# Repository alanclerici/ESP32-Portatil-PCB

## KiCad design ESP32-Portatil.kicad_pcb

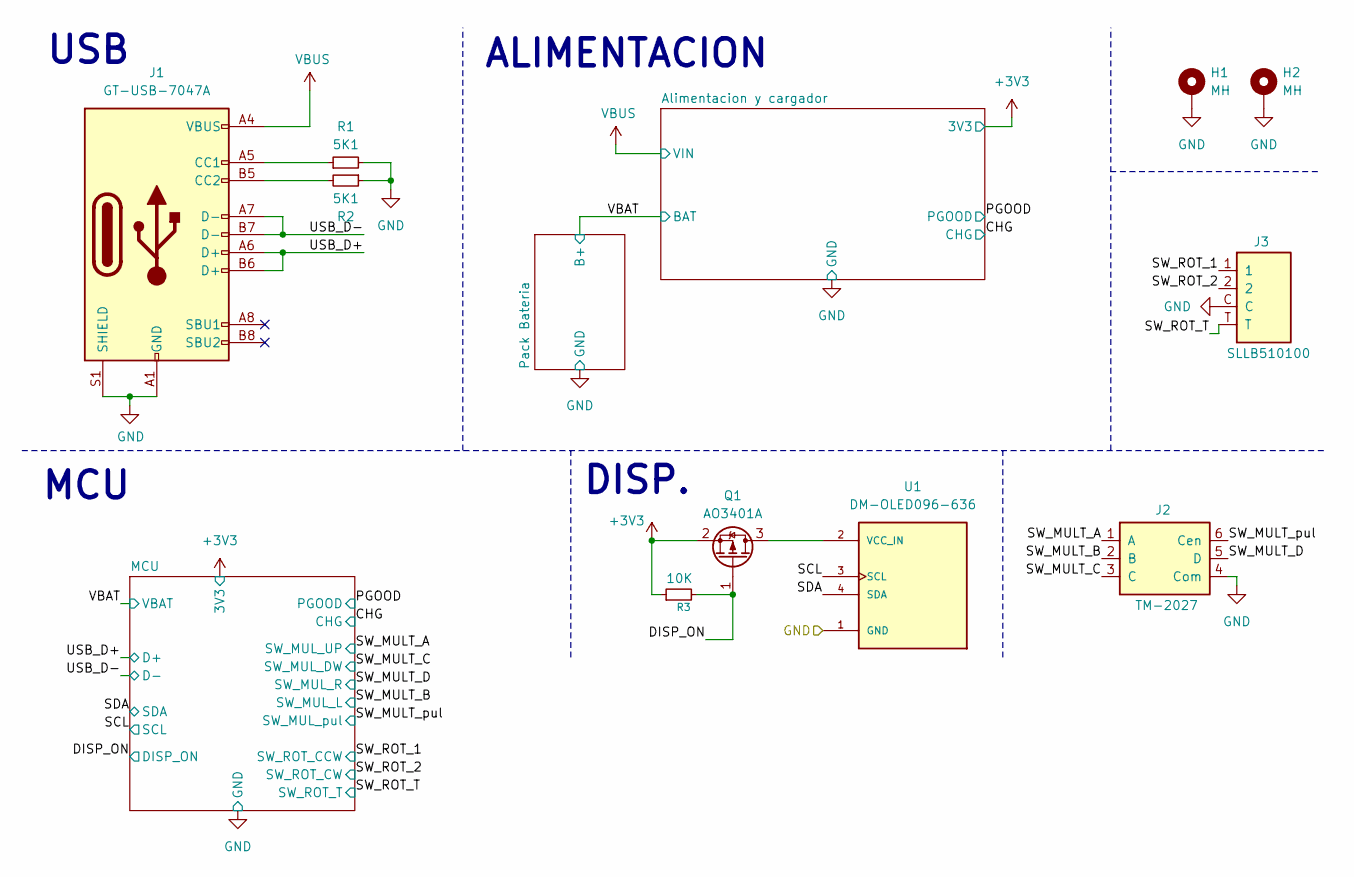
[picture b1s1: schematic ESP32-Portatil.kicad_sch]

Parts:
H1, H2: MH; MountingHole_3.2mm_M3_Pad_Via
J1: GT-USB-7047A; USB_C_Receptacle_GCT_USB4110; LCSC GT-USB-7047A
J2: TM-2027; JLCPCB Part # C318948
J3: SLLB510100; JLCPCB Part # C125039
Q1: AO3401A; SOT-23; JLCPCB Part # C15127
R1, R2: 5K1; R_0402_1005Metric; LCSC 0603WAF5101T5E
R3: 10K; R_0402_1005Metric; JLCPCB Part # C25744
U1: DM-OLED096-636; MODULE_DM-OLED096-636; PARTREV 2018-09-10

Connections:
+3V3: Q1.2 (S), R3.1; also elsewhere on the board
/DISP_ON: Q1.1 (G), R3.2; also elsewhere on the board
/SCL: U1.3 (SCL); also elsewhere on the board
/SDA: U1.4 (SDA); also elsewhere on the board
/SW_MULT_A: J2.1 (A); also elsewhere on the board
/SW_MULT_B: J2.2 (B); also elsewhere on the board
/SW_MULT_C: J2.3 (C); also elsewhere on the board
/SW_MULT_D: J2.5 (D); also elsewhere on the board
/SW_MULT_pul: J2.6 (Cen); also elsewhere on the board
/SW_ROT_1: J3.1; also elsewhere on the board
/SW_ROT_2: J3.2; also elsewhere on the board
/SW_ROT_T: J3.T; also elsewhere on the board
/USB_D+: J1.A6 (D+), J1.B6 (D+); also elsewhere on the board
/USB_D-: J1.A7 (D-), J1.B7 (D-); also elsewhere on the board
GND: H1.1, H2.1, J1.A1 (GND), J1.A12 (GND), J1.B1 (GND), J1.B12 (GND), J1.S1 (SHIELD), J2.4 (Com), J3.C, R1.2, R2.1, U1.1 (GND); also elsewhere on the board
unnamed: J1.A5 (CC1), R1.1
unnamed: J1.B5 (CC2), R2.2
unnamed: Q1.3 (D), U1.2 (VCC_IN)
VBUS: J1.A4 (VBUS), J1.A9 (VBUS), J1.B4 (VBUS), J1.B9 (VBUS); also elsewhere on the board

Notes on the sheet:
DISP.
MCU
USB
ALIMENTACION

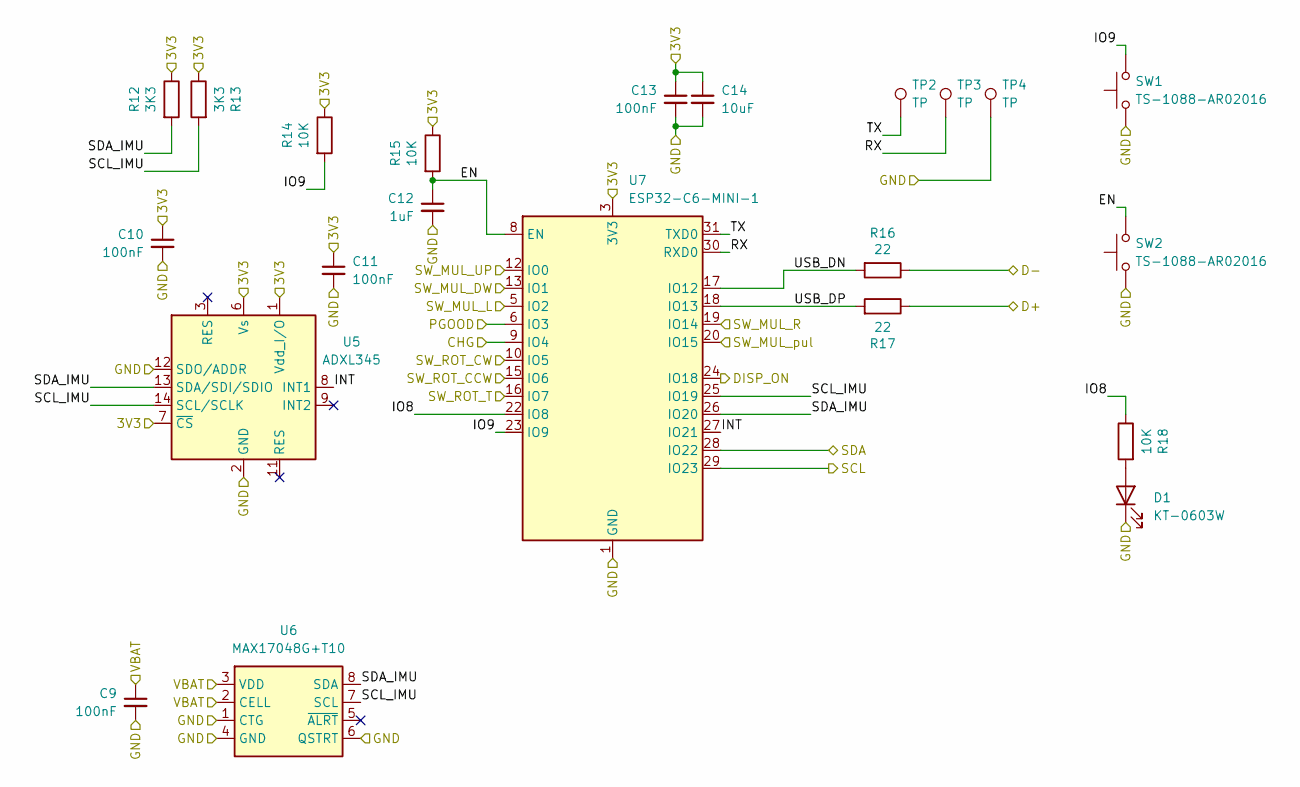
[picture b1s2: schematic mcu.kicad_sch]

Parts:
C9, C10, C11, C13: 100nF; C_0402_1005Metric; JLCPCB Part # C1525
C12: 1uF; C_0402_1005Metric; JLCPCB Part # C52923
C14: 10uF; C_0603; JLCPCB Part # C19702
D1: KT-0603W; LED_0603_1608Metric; LCSC SZYY0603G1
R12, R13: 3K3; R_0402_1005Metric; JLCPCB Part # C25890
R14, R15, R18: 10K; R_0402_1005Metric; LCSC 0603WAF4700T5E
R16, R17: 22; R_0402_1005Metric; LCSC 0402WGF270JTCE
SW1, SW2: TS-1088-AR02016; JLCPCB Part # C720477
TP2, TP3, TP4: TP; TestPoint_Pad_D1.5mm
U5: ADXL345; LGA-14_3x5mm_P0.8mm_LayoutBorder1x6y; JLCPCB Part # C9667
U6: MAX17048G+T10; TDFN-8-1EP_2x2mm_P0.5mm_EP0.8x1.2mm; JLCPCB Part # C2682616
U7: ESP32-C6-MINI-1; JLCPCB Part # C5736265

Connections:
+3V3: C10.1, C11.1, C13.1, C14.1, R12.1, R13.1, R14.1, R15.1, U5.1 (Vdd_I/O), U5.6 (Vs), U5.7 (~CS), U7.3 (3V3); also elsewhere on the board
/CHG: U7.9 (IO4); also elsewhere on the board
/DISP_ON: U7.24 (IO18); also elsewhere on the board
/MCU/EN: C12.1, R15.2, SW2.2, U7.8 (EN)
/MCU/INT: U5.8 (INT1), U7.27 (IO21)
/MCU/IO8: R18.1, U7.22 (IO8)
/MCU/IO9: R14.2, SW1.2, U7.23 (IO9)
/MCU/RX: TP3.1, U7.30 (RXD0)
/MCU/SCL_IMU: R13.2, U5.14 (SCL/SCLK), U6.7 (SCL), U7.25 (IO19)
/MCU/SDA_IMU: R12.2, U5.13 (SDA/SDI/SDIO), U6.8 (SDA), U7.26 (IO20)
/MCU/TX: TP2.1, U7.31 (TXD0)
/MCU/USB_DN: R16.2, U7.17 (IO12)
/MCU/USB_DP: R17.2, U7.18 (IO13)
/PGOOD: U7.6 (IO3); also elsewhere on the board
/SCL: U7.29 (IO23); also elsewhere on the board
/SDA: U7.28 (IO22); also elsewhere on the board
/SW_MULT_A: U7.12 (IO0); also elsewhere on the board
/SW_MULT_B: U7.5 (IO2); also elsewhere on the board
/SW_MULT_C: U7.13 (IO1); also elsewhere on the board
/SW_MULT_D: U7.19 (IO14); also elsewhere on the board
/SW_MULT_pul: U7.20 (IO15); also elsewhere on the board
/SW_ROT_1: U7.15 (IO6); also elsewhere on the board
/SW_ROT_2: U7.10 (IO5); also elsewhere on the board
/SW_ROT_T: U7.16 (IO7); also elsewhere on the board
/USB_D+: R17.1; also elsewhere on the board
/USB_D-: R16.1; also elsewhere on the board
/VBAT: C9.1, U6.2 (CELL), U6.3 (VDD); also elsewhere on the board
GND: C9.2, C10.2, C11.2, C12.2, C13.2, C14.2, D1.1 (K), SW1.1, SW2.1, TP4.1, U5.2 (GND), U5.4 (GND), U5.5 (GND), U5.12 (SDO/ADDR), U6.1 (CTG), U6.4 (GND), U6.6 (QSTRT), U6.9 (EP), U7.1 (GND), U7.2 (GND), U7.11 (GND), U7.14 (GND), U7.36 (GND), U7.37 (GND), U7.38 (GND), U7.39 (GND), U7.40 (GND), U7.41 (GND), U7.42 (GND), U7.43 (GND), U7.44 (GND), U7.45 (GND), U7.46 (GND), U7.47 (GND), U7.48 (GND), U7.49 (GND), U7.50 (GND), U7.51 (GND), U7.52 (GND), U7.53 (GND); also elsewhere on the board
unnamed: D1.2 (A), R18.2

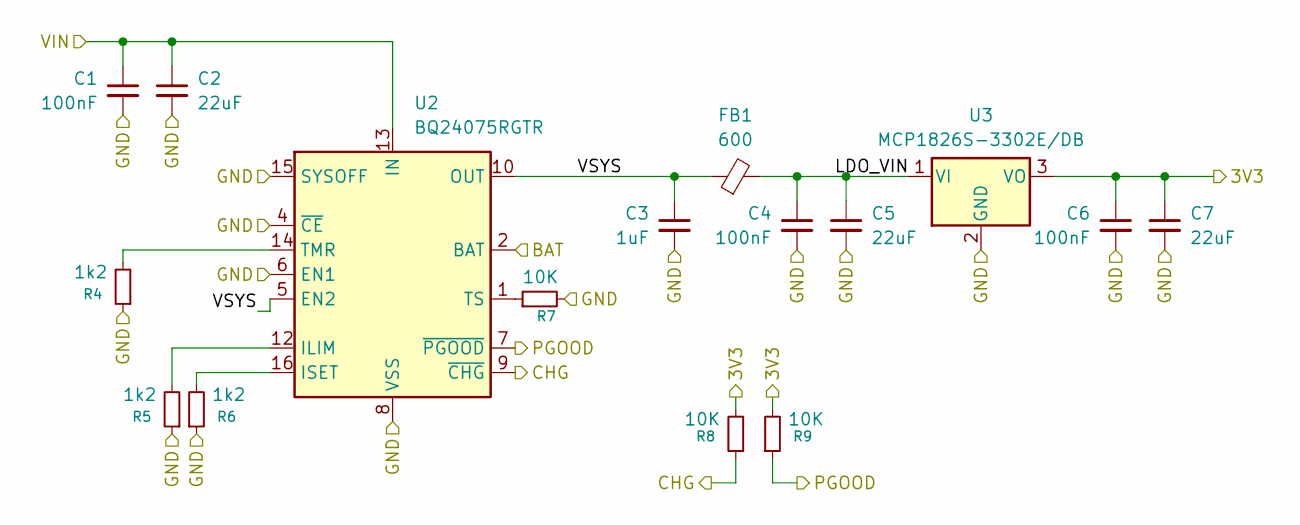
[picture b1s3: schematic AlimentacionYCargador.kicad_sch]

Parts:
C1, C4, C6: 100nF; C_0402_1005Metric; JLCPCB Part # C1525
C2, C5, C7: 22uF; C_0805_2012Metric; JLCPCB Part # C45783
C3: 1uF; C_0402_1005Metric; JLCPCB Part # C52923
FB1: 600; L_0805_2012Metric; JLCPCB Part # C1017
R4, R5, R6: 1k2; R_0402_1005Metric; JLCPCB Part # C25862
R7, R8, R9: 10K; R_0402_1005Metric; JLCPCB Part # C25744
U2: BQ24075RGTR; VQFN-16-1EP_3x3mm_P0.5mm_EP1.6x1.6mm; JLCPCB Part # C15464
U3: MCP1826S-3302E/DB; SOT-223-3_TabPin2; JLCPCB Part # C638624

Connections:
+3V3: C6.1, C7.1, R8.2, R9.2, U3.3 (VO); also elsewhere on the board
/Alimentacion y cargador/LDO_VIN: C4.1, C5.1, FB1.2, U3.1 (VI)
/Alimentacion y cargador/VSYS: C3.1, FB1.1, U2.5 (EN2), U2.10 (OUT), U2.11 (OUT)
/CHG: R8.1, U2.9 (~CHG); also elsewhere on the board
/PGOOD: R9.1, U2.7 (~PGOOD); also elsewhere on the board
/VBAT: U2.2 (BAT), U2.3 (BAT); also elsewhere on the board
GND: C1.2, C2.2, C3.2, C4.2, C5.2, C6.2, C7.2, R4.1, R5.1, R6.1, R7.2, U2.4 (~CE), U2.6 (EN1), U2.8 (VSS), U2.15 (SYSOFF), U2.17 (VSS), U3.2 (GND); also elsewhere on the board
unnamed: R5.2, U2.12 (ILIM)
unnamed: R6.2, U2.16 (ISET)
unnamed: R4.2, U2.14 (TMR)
unnamed: R7.1, U2.1 (TS)
VBUS: C1.1, C2.1, U2.13 (IN); also elsewhere on the board

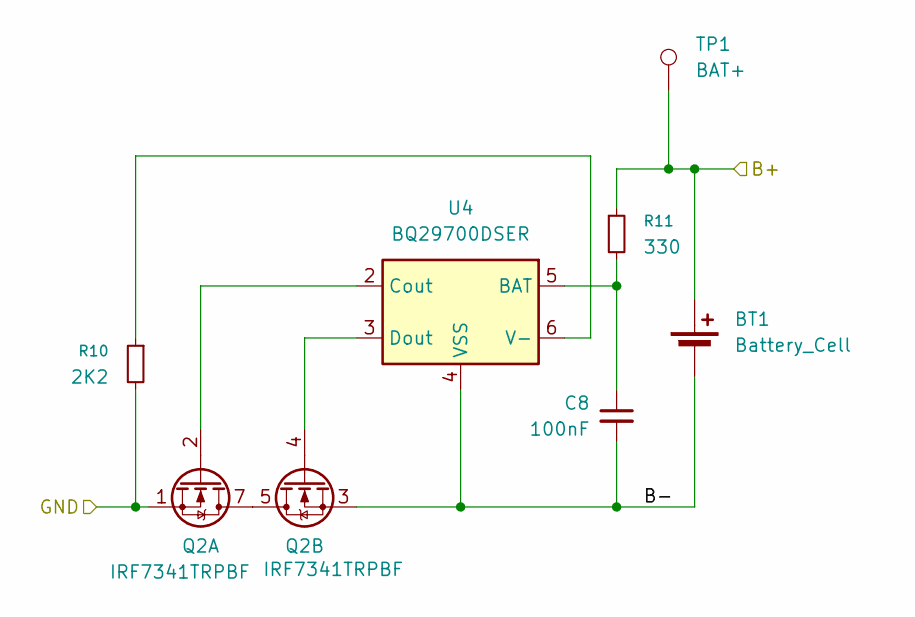
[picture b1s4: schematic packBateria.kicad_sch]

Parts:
BT1: Battery_Cell; BatteryHolder_18650
C8: 100nF; C_0402_1005Metric; JLCPCB Part # C1525
Q2: IRF7341TRPBF; SOIC-8_3.9x4.9mm_P1.27mm; JLCPCB Part # C21791
R10: 2K2; R_0402_1005Metric; JLCPCB Part # C25879
R11: 330; R_0603_1608Metric; JLCPCB Part # C23138
TP1: BAT+; TestPoint_Loop_D1.80mm_Drill1.0mm_Beaded
U4: BQ29700DSER; WSON-6_1.5x1.5mm_P0.5mm; JLCPCB Part # C183096

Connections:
/Pack Bateria/B-: BT1.2 (-), C8.2, Q2.3 (S2), U4.4 (VSS)
/VBAT: BT1.1 (+), R11.1, TP1.1; also elsewhere on the board
GND: Q2.1 (S1), R10.2; also elsewhere on the board
unnamed: Q2.5 (D2), Q2.6 (D2), Q2.7 (D1), Q2.8 (D1)
unnamed: Q2.2 (G1), U4.2 (Cout)
unnamed: Q2.4 (G2), U4.3 (Dout)
unnamed: C8.1, R11.2, U4.5 (BAT)
unnamed: R10.1, U4.6 (V-)

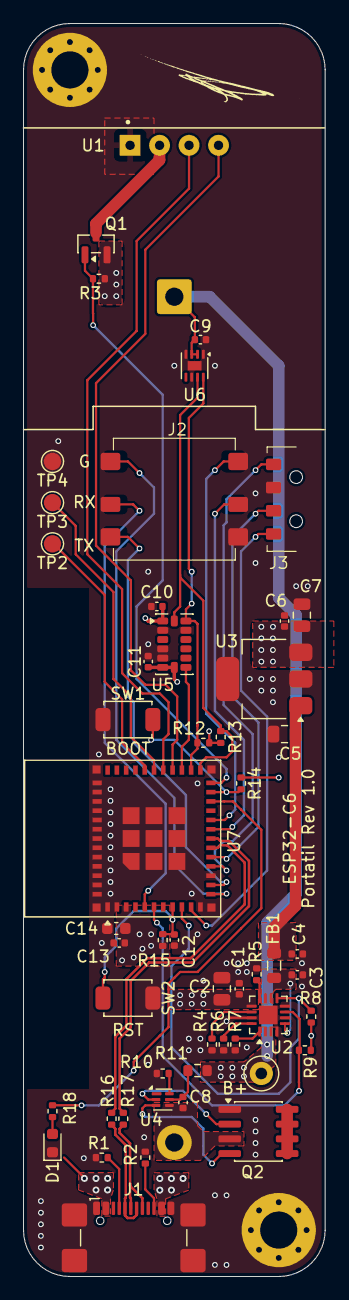
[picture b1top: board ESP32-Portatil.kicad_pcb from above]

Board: 4 copper layers, 26.0 x 108.0 mm, 55 parts (1 on the bottom side), 45 nets.

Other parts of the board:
B+: BAT+; TestPoint_Loop_D1.80mm_Drill1.0mm_Beaded

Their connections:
/VBAT: B+.1; also elsewhere on the board

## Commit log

2026-05-28 Creacion del repo
2026-06-03 Avance de sch
2026-06-04 Casi que placa lista
2026-06-17 listo para fabricar
2026-06-17 Fabricado
